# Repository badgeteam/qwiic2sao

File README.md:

# QWIIC to SAO adapter

Untested, might explode, you've been warned.

## License

Copyright 2023 Nicolai Electronics

This hardware design may be used under the terms of the [CERN-OHL-P](LICENSE) license.

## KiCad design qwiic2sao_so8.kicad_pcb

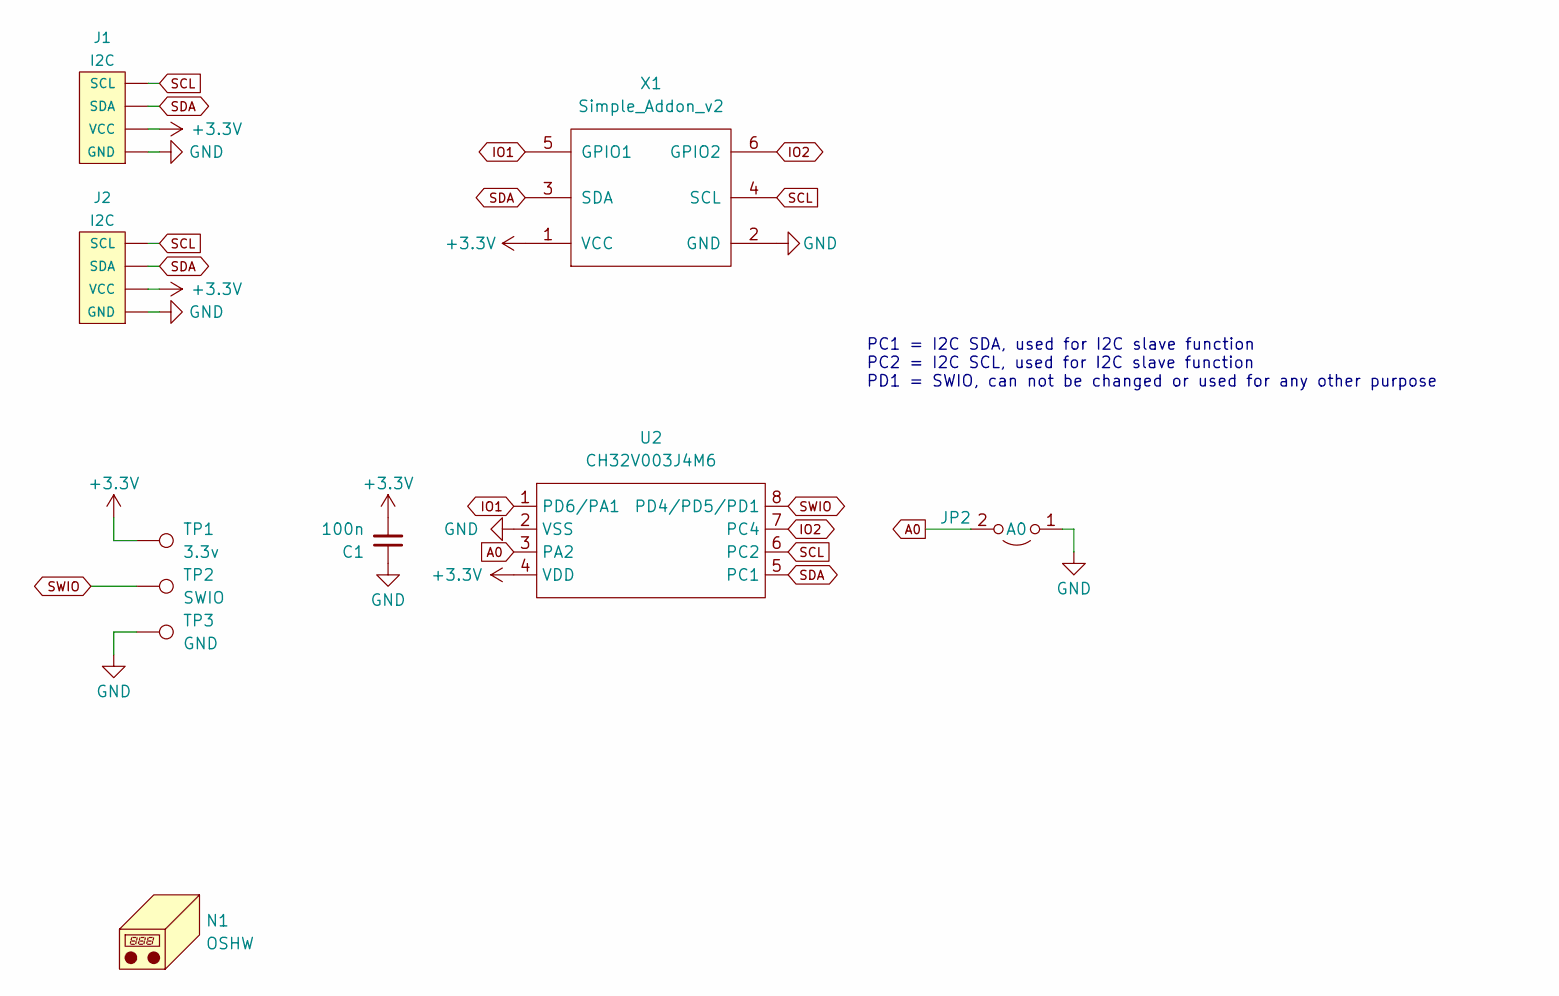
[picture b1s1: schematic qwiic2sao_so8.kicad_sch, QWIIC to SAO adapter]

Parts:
C1: 100n; C_0805_2012Metric
J1, J2: I2C; 1X04_1MM_RA_GND; LCSC C160404
JP2: A0; SolderJumper-2_P1.3mm_Open_TrianglePad1.0x1.5mm
N1: OSHW; OSHW-Logo2_7.3x6mm_Mask
TP1: 3.3v; TestPoint_Pad_D2.0mm
TP2: SWIO; TestPoint_Pad_D2.0mm
TP3: GND; TestPoint_Pad_D2.0mm
U2: CH32V003J4M6; SSOP-8_3.9x5.05mm_P1.27mm
X1: Simple_Addon_v2; Simple_Addon_v2-BADGE-2x3

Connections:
+3.3V: C1.2, J1.2 (VCC), J2.2 (VCC), TP1.1, U2.4 (VDD), X1.1 (VCC)
A0: JP2.2 (B), U2.3 (PA2)
GND: C1.1, J1.1 (GND), J1.5, J1.6, J2.1 (GND), J2.5, J2.6, JP2.1 (A), TP3.1, U2.2 (VSS), X1.2 (GND)
IO1: U2.1 (PD6/PA1), X1.5 (GPIO1)
IO2: U2.7 (PC4), X1.6 (GPIO2)
SCL: J1.4 (SCL), J2.4 (SCL), U2.6 (PC2), X1.4 (SCL)
SDA: J1.3 (SDA), J2.3 (SDA), U2.5 (PC1), X1.3 (SDA)
SWIO: TP2.1, U2.8 (PD4/PD5/PD1)

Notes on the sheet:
PC1 = I2C SDA, used for I2C slave function PC2 = I2C SCL, used for I2C slave function PD1 = SWIO, can not be changed or used for any other purpose

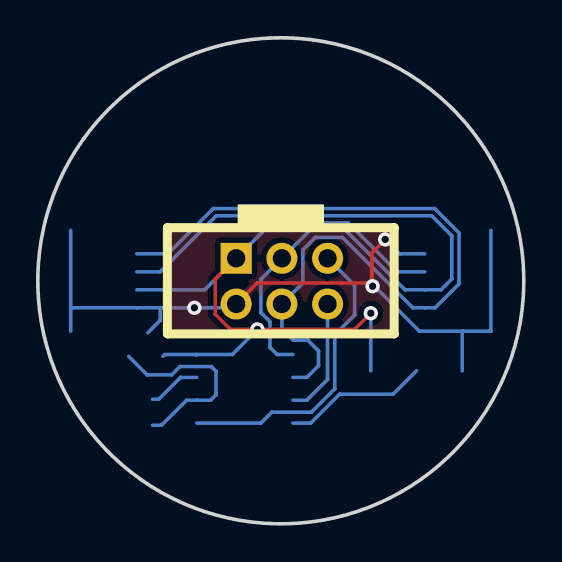
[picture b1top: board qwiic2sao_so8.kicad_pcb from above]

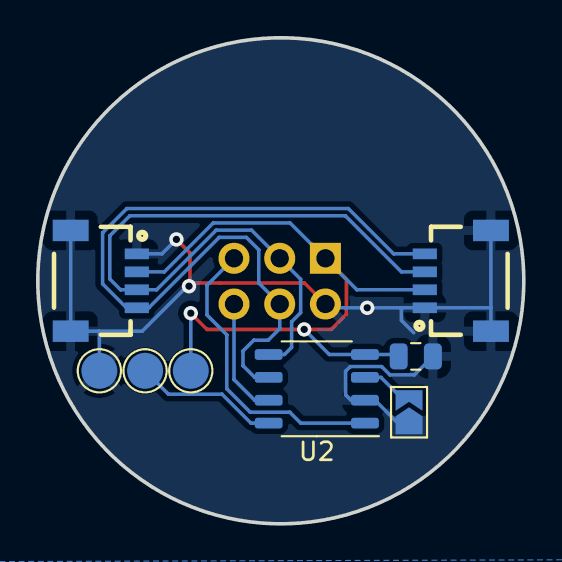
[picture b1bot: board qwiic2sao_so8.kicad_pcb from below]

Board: 2 copper layers, 27.0 x 27.0 mm, 10 parts (9 on the bottom side), 8 nets.

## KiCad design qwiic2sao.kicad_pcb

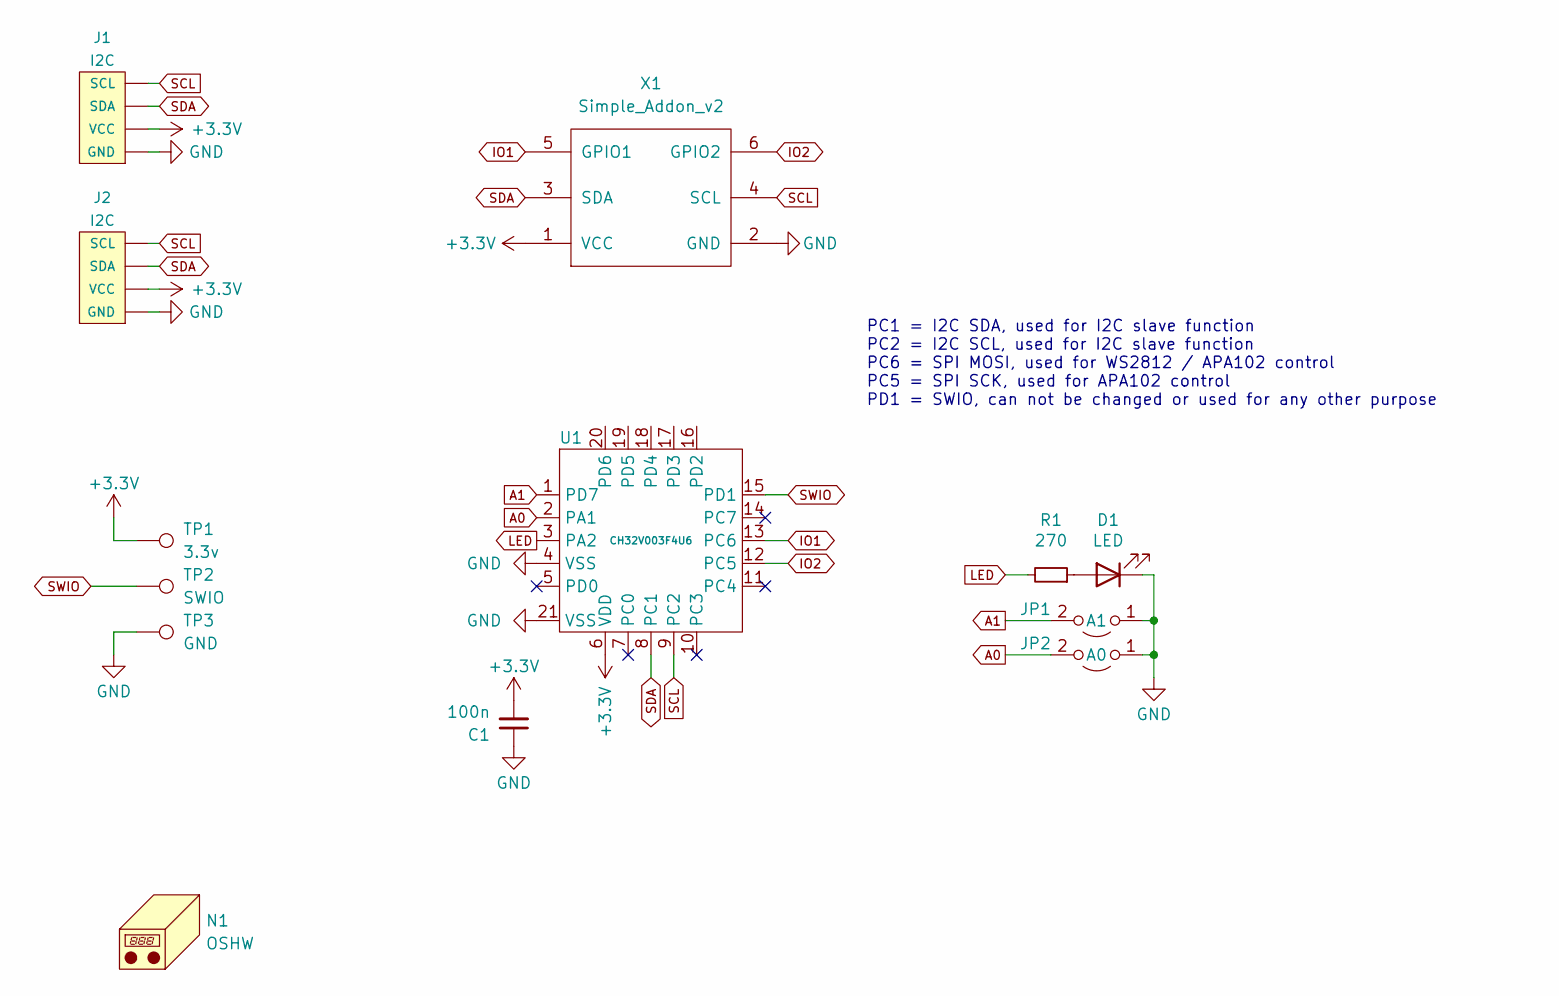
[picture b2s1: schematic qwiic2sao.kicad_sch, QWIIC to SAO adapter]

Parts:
C1: 100n; C_0402_1005Metric
D1: LED; LED_0603_1608Metric; LCSC C264473
J1, J2: I2C; 1X04_1MM_RA_GND; LCSC C160404
JP1: A1; SolderJumper-2_P1.3mm_Open_TrianglePad1.0x1.5mm
JP2: A0; SolderJumper-2_P1.3mm_Open_TrianglePad1.0x1.5mm
N1: OSHW; OSHW-Logo2_7.3x6mm_Mask
R1: 270; R_0402_1005Metric; LCSC C22966
TP1: 3.3v; TestPoint_Pad_D2.0mm
TP2: SWIO; TestPoint_Pad_D2.0mm
TP3: GND; TestPoint_Pad_D2.0mm
U1: CH32V003F4U6; QFN-20-1EP_3x3mm_P0.4mm_EP1.65x1.65mm; LCSC C5299908
X1: Simple_Addon_v2; Simple_Addon_v2-BADGE-2x3

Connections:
+3.3V: C1.2, J1.2 (VCC), J2.2 (VCC), TP1.1, U1.6 (VDD), X1.1 (VCC)
A0: JP2.2 (B), U1.2 (PA1)
A1: JP1.2 (B), U1.1 (PD7)
GND: C1.1, D1.1 (K), J1.1 (GND), J1.5, J1.6, J2.1 (GND), J2.5, J2.6, JP1.1 (A), JP2.1 (A), TP3.1, U1.4 (VSS), U1.21 (VSS), X1.2 (GND)
IO1: U1.13 (PC6), X1.5 (GPIO1)
IO2: U1.12 (PC5), X1.6 (GPIO2)
LED: R1.2, U1.3 (PA2)
unnamed: D1.2 (A), R1.1
SCL: J1.4 (SCL), J2.4 (SCL), U1.9 (PC2), X1.4 (SCL)
SDA: J1.3 (SDA), J2.3 (SDA), U1.8 (PC1), X1.3 (SDA)
SWIO: TP2.1, U1.15 (PD1)

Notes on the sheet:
PC1 = I2C SDA, used for I2C slave function PC2 = I2C SCL, used for I2C slave function PC6 = SPI MOSI, used for WS2812 / APA102 control PC5 = SPI SCK, used for APA102 control PD1 = SWIO, can not be changed or used for any other purpose

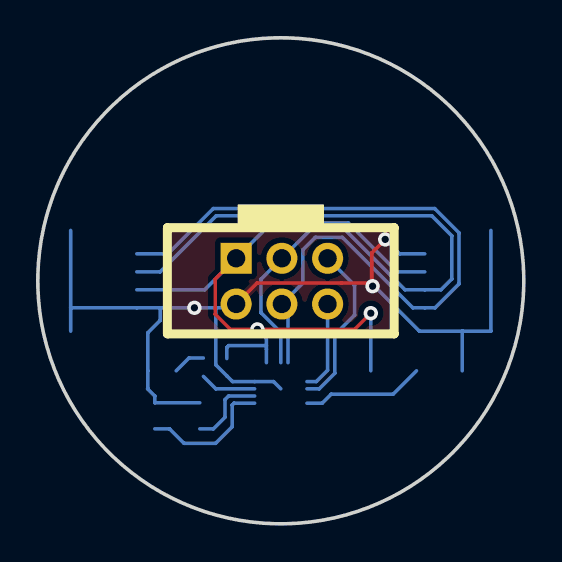
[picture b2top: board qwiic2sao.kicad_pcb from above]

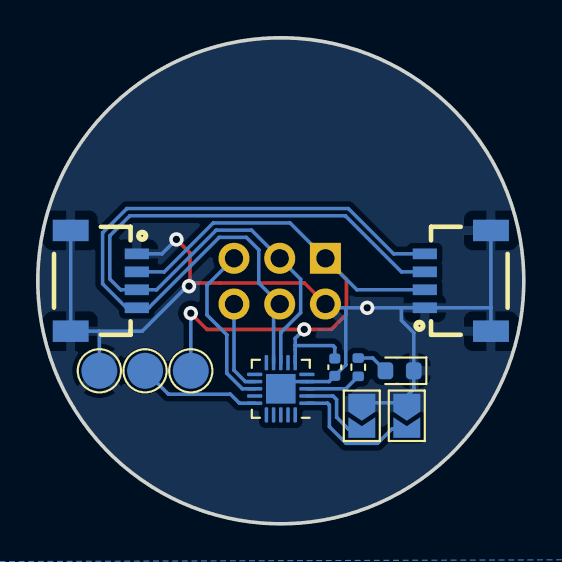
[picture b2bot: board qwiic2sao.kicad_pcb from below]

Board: 2 copper layers, 27.0 x 27.0 mm, 13 parts (12 on the bottom side), 11 nets.

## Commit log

2024-01-05 Add SO8 hand-soldering version
